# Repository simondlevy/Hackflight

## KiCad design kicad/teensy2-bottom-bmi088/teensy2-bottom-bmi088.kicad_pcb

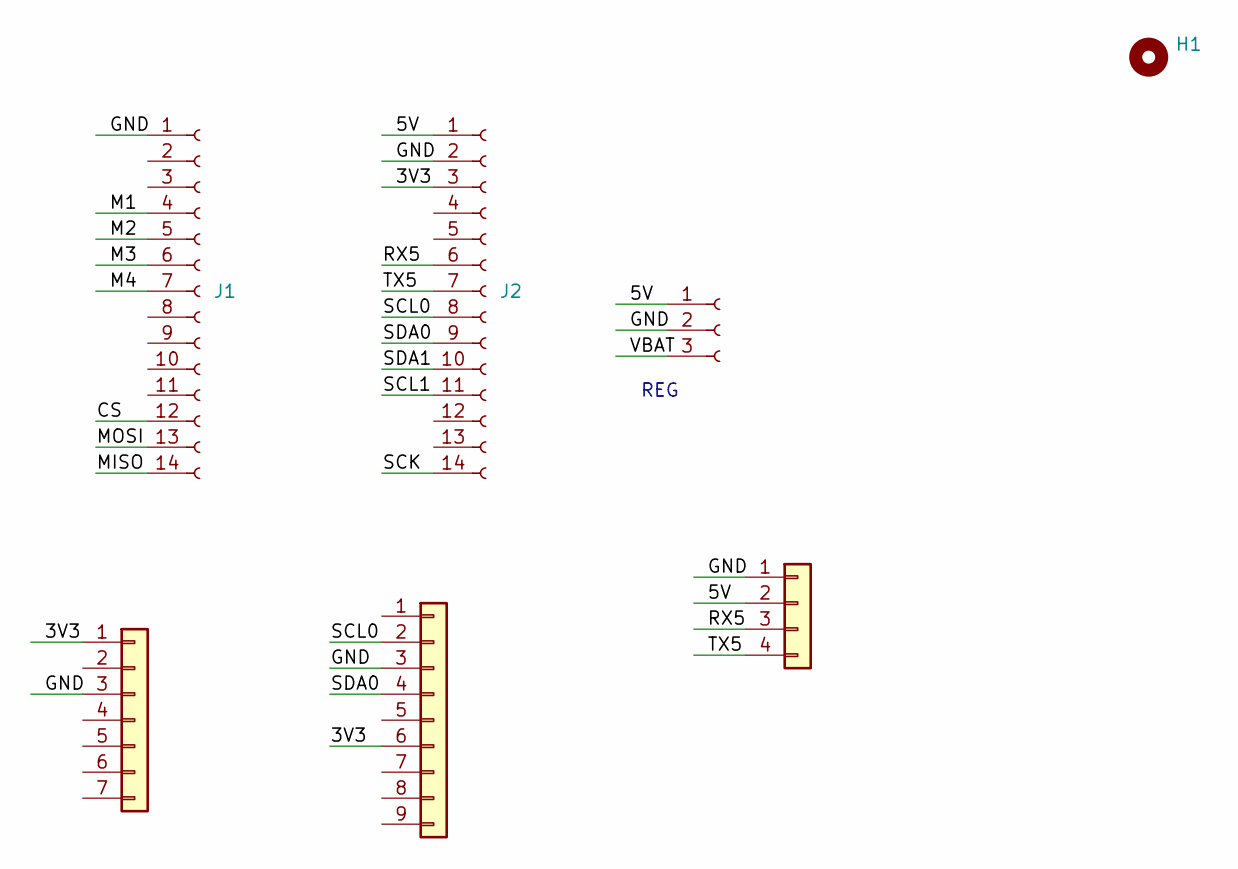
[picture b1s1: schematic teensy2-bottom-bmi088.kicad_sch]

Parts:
H1: MountingHole; MountingHole_2.5mm
J1: Conn_01x14; PinSocket_1x14_P2.54mm_Vertical
J2: Conn_01x14_Socket; PinSocket_1x14_P2.54mm_Vertical
J3: Conn_01x04; PinHeader_1x04_P2.00mm_Vertical
J4: Conn_01x03_Socket; PinHeader_1x03_P2.54mm_Vertical
J7: Conn_01x07; PinHeader_1x07_P1.27mm_Vertical
J8: Conn_01x09; PinHeader_1x09_P1.27mm_Vertical

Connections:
/3V3: J2.3, J7.1, J8.6
/5V: J2.1, J3.2, J4.1
/CS: J1.12
/GND: J1.1, J2.2, J3.1, J4.2, J7.3, J8.3
/M1: J1.4
/M2: J1.5
/M3: J1.6
/M4: J1.7
/MISO: J1.14
/MOSI: J1.13
/RX5: J2.6, J3.3
/SCK: J2.14
/SCL0: J2.8, J8.2
/SCL1: J2.11
/SDA0: J2.9, J8.4
/SDA1: J2.10
/TX5: J2.7, J3.4
/VBAT: J4.3

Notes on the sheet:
REG

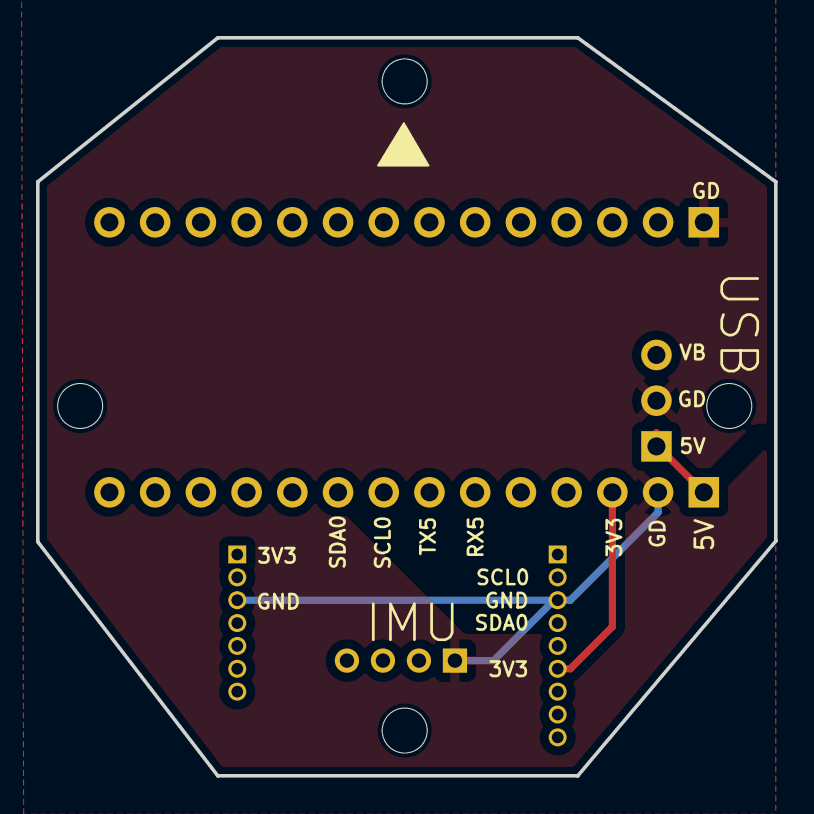
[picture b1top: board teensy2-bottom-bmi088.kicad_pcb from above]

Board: 2 copper layers, 41.0 x 41.0 mm, 8 parts (0 on the bottom side), 7 nets.

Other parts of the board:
H1#2: MountingHole; MountingHole_2.5mm

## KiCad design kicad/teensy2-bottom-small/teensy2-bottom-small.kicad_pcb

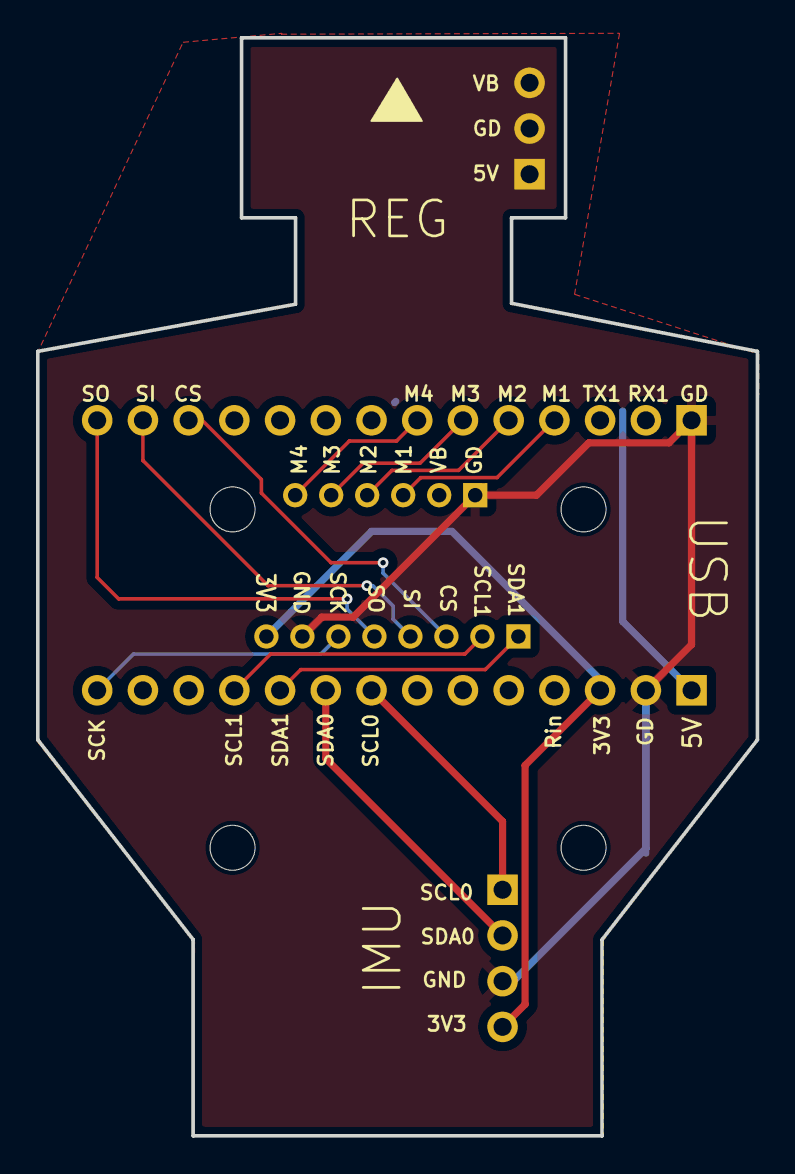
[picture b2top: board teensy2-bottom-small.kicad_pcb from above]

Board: 2 copper layers, 40.0 x 61.0 mm, 10 parts (0 on the bottom side), 16 nets.

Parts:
H1, H2, H3, H4: MountingHole; MountingHole_2.5mm
J1, J2: Conn_01x14_Socket; PinSocket_1x14_P2.54mm_Vertical
J3: Conn_01x04_Socket; PinHeader_1x04_P2.54mm_Vertical
J4: Conn_01x03_Socket; PinHeader_1x03_P2.54mm_Vertical
J5: Conn_01x06_Pin; PinHeader_1x06_P2.00mm_Vertical
J7: Conn_01x08_Pin; PinSocket_1x08_P2.00mm_Vertical

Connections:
/3V3: J2.3, J3.4, J7.8
/5V: J2.1, J4.1
/CS: J1.12, J7.3
/GND: J1.1, J2.2, J3.3, J4.2, J5.1, J7.7
/M1: J1.4, J5.3
/M2: J1.5, J5.4
/M3: J1.6, J5.5
/M4: J1.7, J5.6
/MISO: J1.14, J7.5
/MOSI: J1.13, J7.4
/SCK: J2.14, J7.6
/SCL0: J2.8, J3.1
/SCL1: J2.11, J7.2
/SDA0: J2.9, J3.2
/SDA1: J2.10, J7.1
/VBAT: J4.3, J5.2

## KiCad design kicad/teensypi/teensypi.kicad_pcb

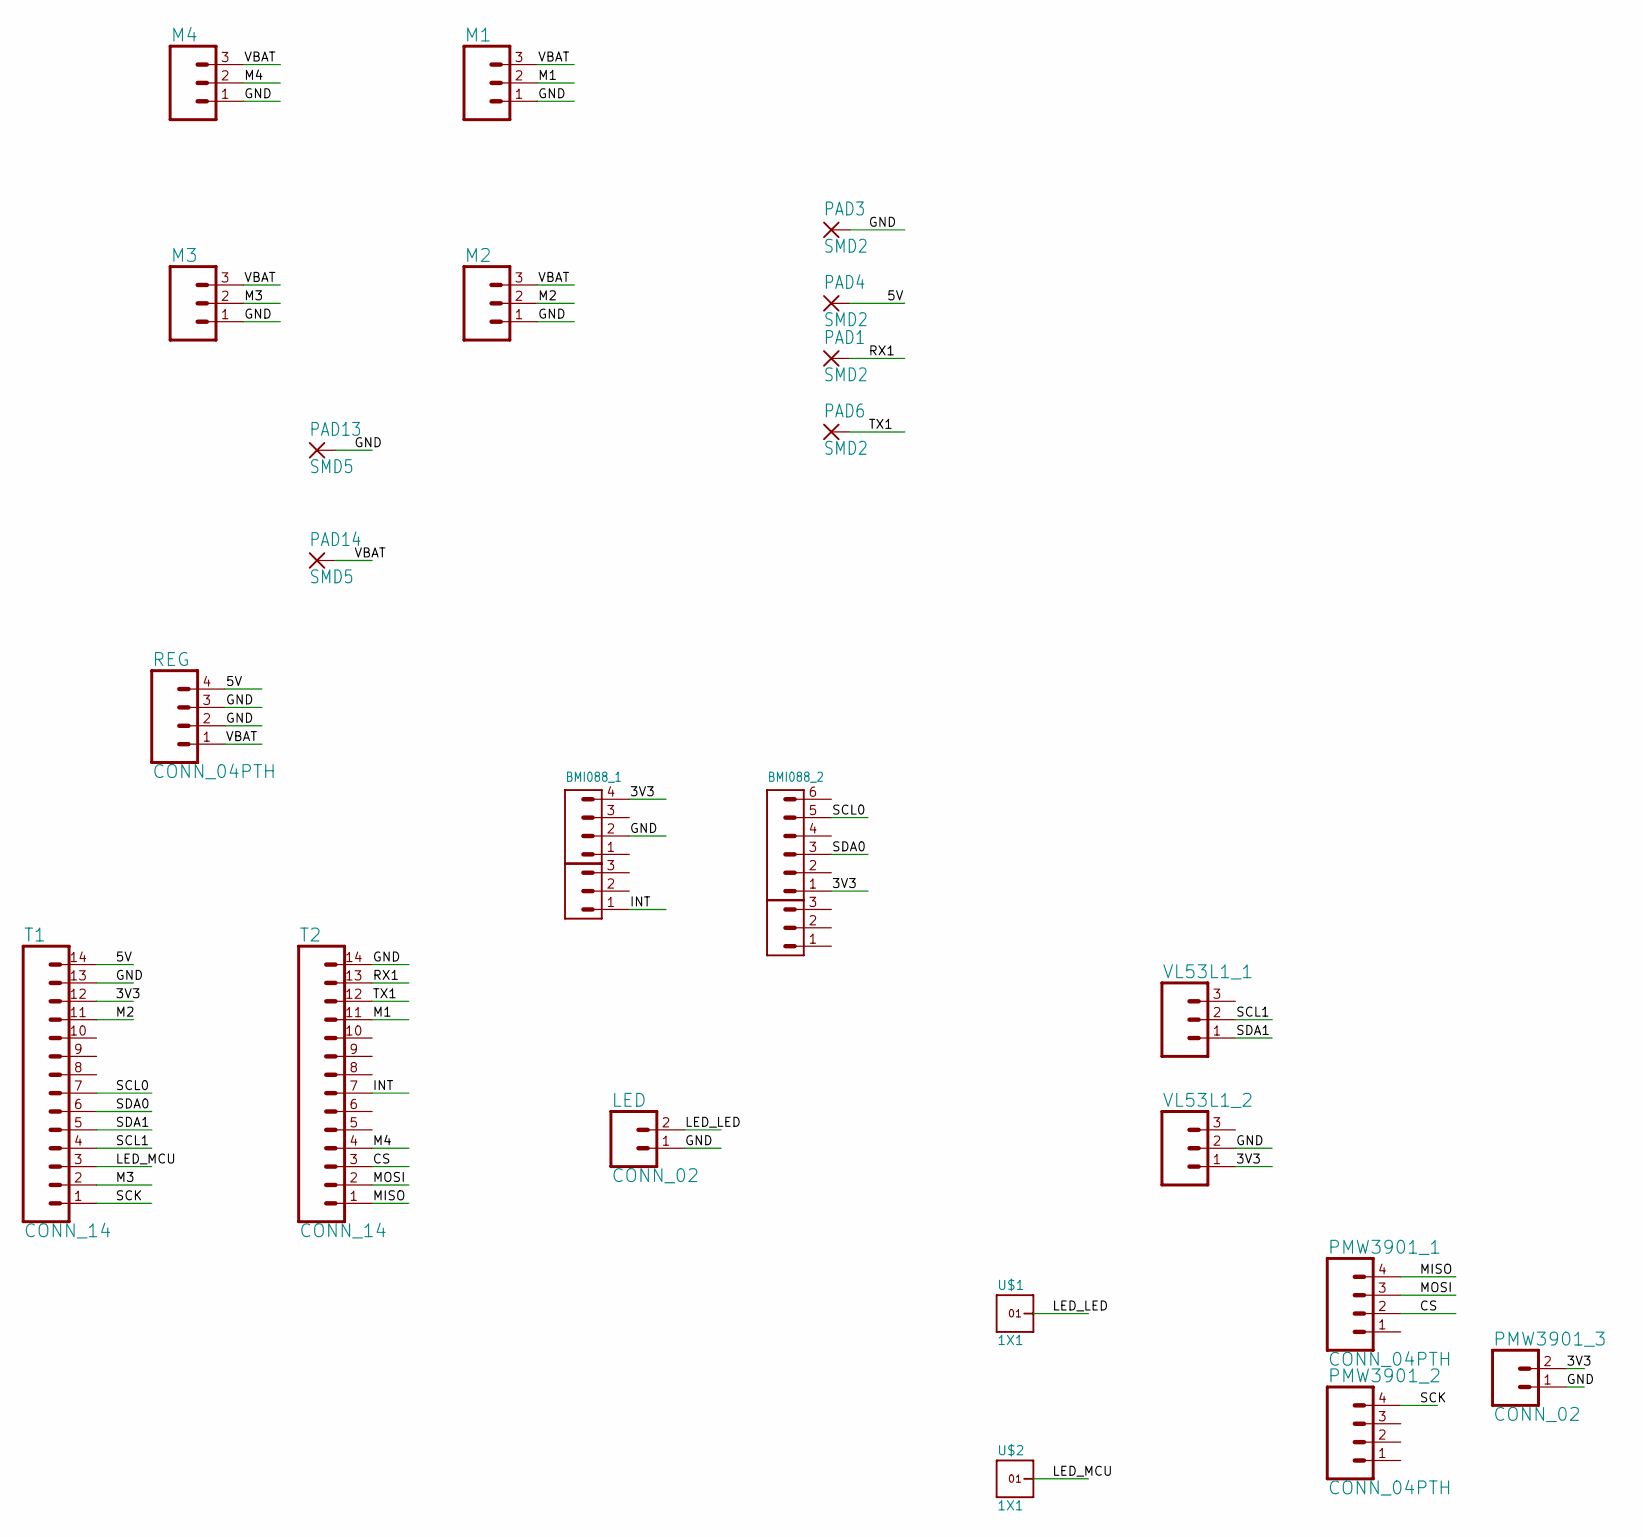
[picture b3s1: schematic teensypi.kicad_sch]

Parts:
BMI088_1: PH1X4-05; PH005-1-4
BMI088_2: PH1X6-05; PH005-1-6
LED: CONN_02; 1X02
M1, M2, M3, M4: 455-1750-1-ND; 1X03
PAD1, PAD3, PAD4, PAD6: SMD2; SMD1,27-2,54
PAD13, PAD14: SMD5; SMD2,54-5,08
PH2, PH3: PH1X3-05; PH005-1-3
PMW3901_1, PMW3901_2: CONN_04PTH; 1X04
PMW3901_3: CONN_02; 1X02
REG: CONN_04PTH; 1X04
T1, T2: CONN_14; 1X14
U$1, U$2: 1X1
VL53L1_1, VL53L1_2: 455-1750-1-ND; 1X03

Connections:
3V3: BMI088_1.4, BMI088_2.1, PMW3901_3.2, T1.12, VL53L1_2.1
5V: PAD4.1, REG.4, T1.14
CS: PMW3901_1.2, T2.3
GND: BMI088_1.2, LED.1, M1.1, M2.1, M3.1, M4.1, PAD3.1, PAD13.1, PMW3901_3.1, REG.2, REG.3, T1.13, T2.14, VL53L1_2.2
INT: PH3.1, T2.7
LED_LED: LED.2, U$1.1
LED_MCU: T1.3, U$2.1
M1: M1.2, T2.11
M2: M2.2, T1.11
M3: M3.2, T1.2
M4: M4.2, T2.4
MISO: PMW3901_1.4, T2.1
MOSI: PMW3901_1.3, T2.2
RX1: PAD1.1, T2.13
SCK: PMW3901_2.4, T1.1
SCL0: BMI088_2.5, T1.7
SCL1: T1.4, VL53L1_1.2
SDA0: BMI088_2.3, T1.6
SDA1: T1.5, VL53L1_1.1
TX1: PAD6.1, T2.12
VBAT: M1.3, M2.3, M3.3, M4.3, PAD14.1, REG.1

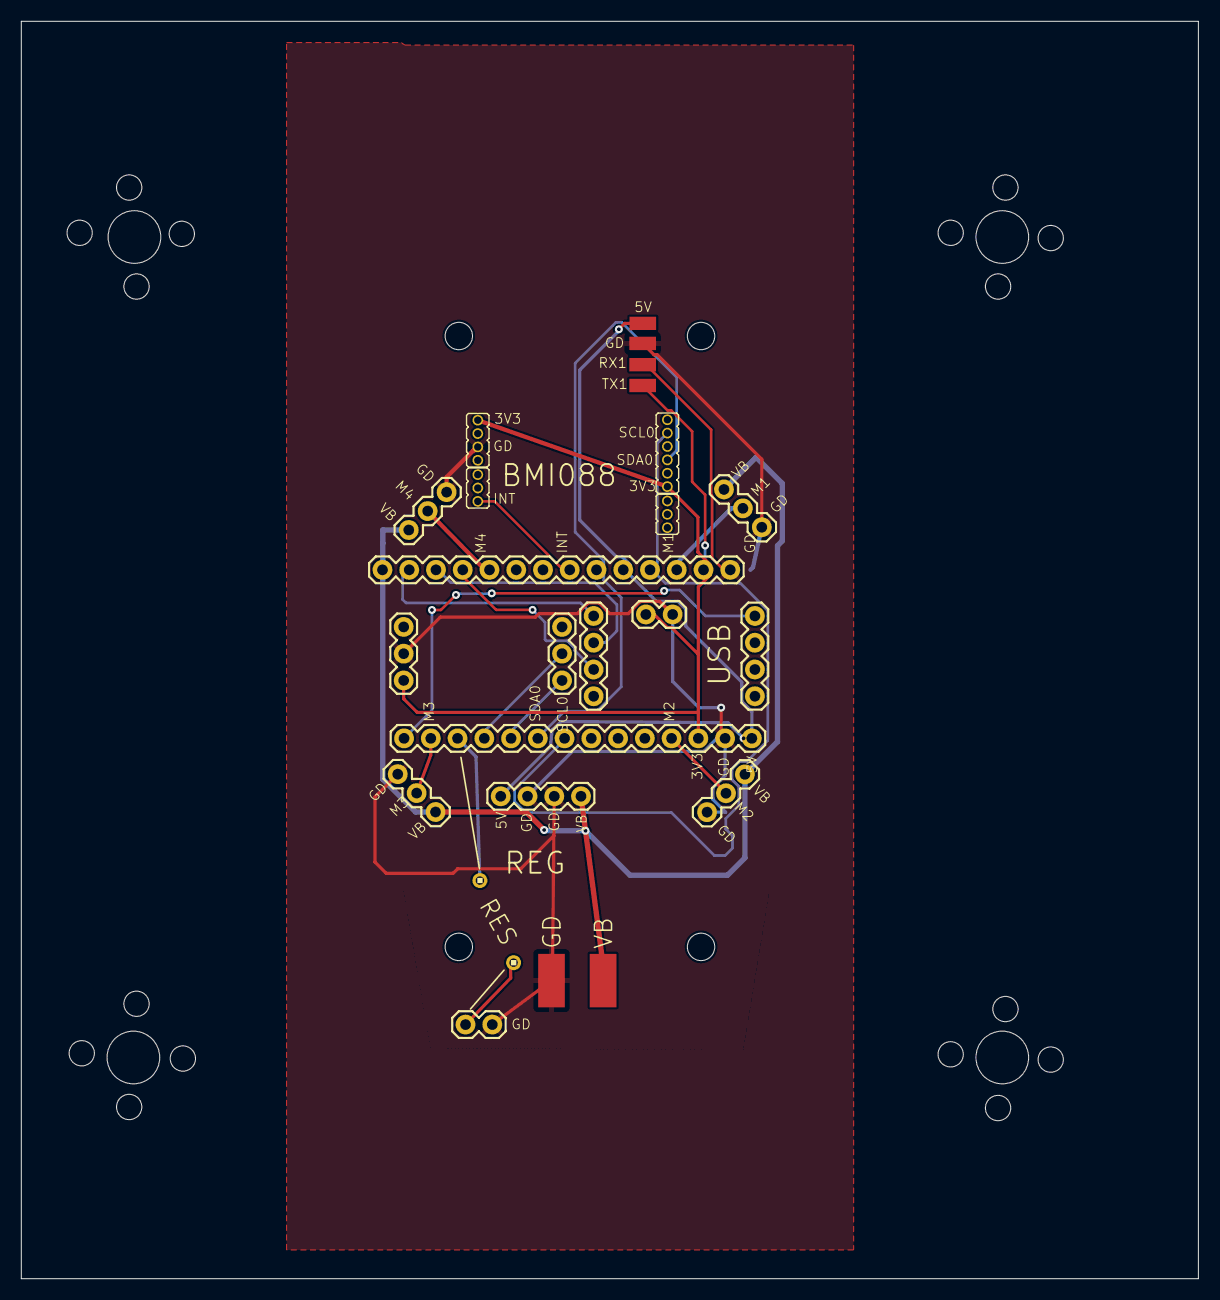
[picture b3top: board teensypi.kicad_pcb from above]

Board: 4 copper layers, 111.8 x 119.4 mm, 49 parts (0 on the bottom side), 21 nets.

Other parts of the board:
@HOLE0, @HOLE1, @HOLE2, @HOLE3, @HOLE4, @HOLE5, @HOLE6, @HOLE7, @HOLE8, @HOLE9, @HOLE10, @HOLE11, @HOLE12, @HOLE13, @HOLE14, @HOLE15, @HOLE16, @HOLE17, @HOLE18, @HOLE19, @HOLE20, @HOLE21, @HOLE22, @HOLE23: (no value)

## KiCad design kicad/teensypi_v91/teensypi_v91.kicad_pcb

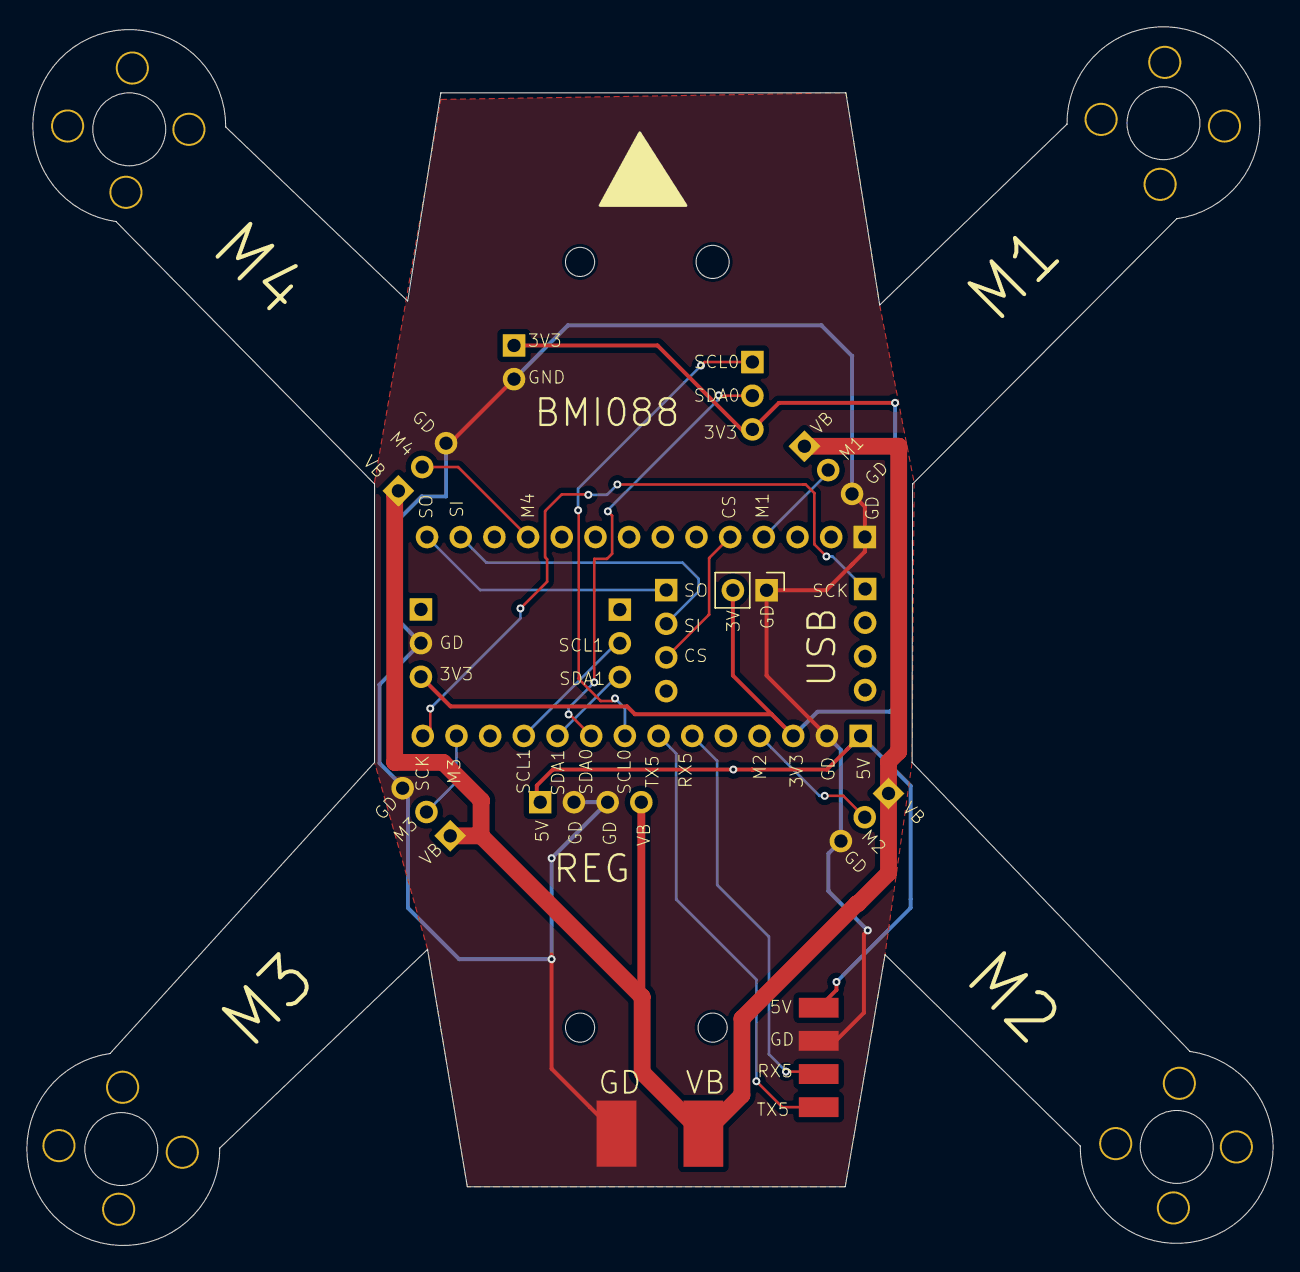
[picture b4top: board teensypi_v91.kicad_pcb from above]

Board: 2 copper layers, 94.0 x 91.9 mm, 44 parts (0 on the bottom side), 18 nets.

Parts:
GND_PAD1, GND_PAD18, GND_PAD19, GND_PAD20, GND_PAD21: Conn_01x01; SolderWirePad_1x01_SMD_5x10mm
M1_center1, M2_center1, M3_center1, M4_center1: MountingHole; MountingHole_5.5mm
M_1_1, M_1_2, M_1_3, M_1_4, M_2_1, M_2_2, M_2_3, M_2_4, M_3_1, M_3_2, M_3_3, M_3_4, M_4_1, M_4_2, M_4_3, M_4_4: MountingHole; MountingHole_2.2mm_M2
Motor5: Conn_01x03_Female; PinHeader_1x03_P2.54mm_Vertical
PMW3901_L1, PMW3901_R1: Conn_01x04_Female; PinSocket_1x04_P2.54mm_Vertical
PMW3901_PWR1, PMW3901_PWR2: Conn_01x02_Female; PinHeader_1x02_P2.54mm_Vertical
POST_1, POST_2, POST_3, POST_4: MountingHole; MountingHole_2.2mm_M2
REG1: Conn_01x04_Female; PinSocket_1x04_P2.54mm_Vertical
Teensy_bottom1: Conn_01x14_Female; PinSocket_1x14_P2.54mm_Vertical
Teensy_top1: Conn_01x14_Female; PinSocket_1x14_P2.54mm_Vertical
VB_PAD1: Conn_01x01; SolderWirePad_1x01_SMD_5x10mm
VL53L1_L1, VL53L1_L2, VL53L1_L3, VL53L1_L4, VL53L1_L5, VL53L1_R1: Conn_01x03_Female; PinHeader_1x03_P2.54mm_Vertical

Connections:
/3V3: Motor5.3, PMW3901_PWR1.2, PMW3901_PWR2.1, Teensy_bottom1.3, VL53L1_L1.3
/5V: GND_PAD19.1, REG1.1, Teensy_bottom1.1
/CS: PMW3901_R1.3, Teensy_top1.5
/GND: GND_PAD1.1, GND_PAD18.1, PMW3901_PWR1.1, PMW3901_PWR2.2, REG1.2, REG1.3, Teensy_bottom1.2, Teensy_top1.1, VL53L1_L1.2, VL53L1_L2.3, VL53L1_L3.3, VL53L1_L4.3, VL53L1_L5.3
/M1: Teensy_top1.4, VL53L1_L2.2
/M2: Teensy_bottom1.4, VL53L1_L3.2
/M3: Teensy_bottom1.13, VL53L1_L5.2
/M4: Teensy_top1.11, VL53L1_L4.2
/MISO: PMW3901_R1.1, Teensy_top1.14
/MOSI: PMW3901_R1.2, Teensy_top1.13
/RX5: GND_PAD20.1, Teensy_bottom1.6
/SCK: PMW3901_L1.1, Teensy_bottom1.14
/SCL0: Motor5.1, Teensy_bottom1.8
/SCL1: Teensy_bottom1.11, VL53L1_R1.2
/SDA0: Motor5.2, Teensy_bottom1.9
/SDA1: Teensy_bottom1.10, VL53L1_R1.3
/TX5: GND_PAD21.1, Teensy_bottom1.7
/VBAT: REG1.4, VB_PAD1.1, VL53L1_L2.1, VL53L1_L3.1, VL53L1_L4.1, VL53L1_L5.1

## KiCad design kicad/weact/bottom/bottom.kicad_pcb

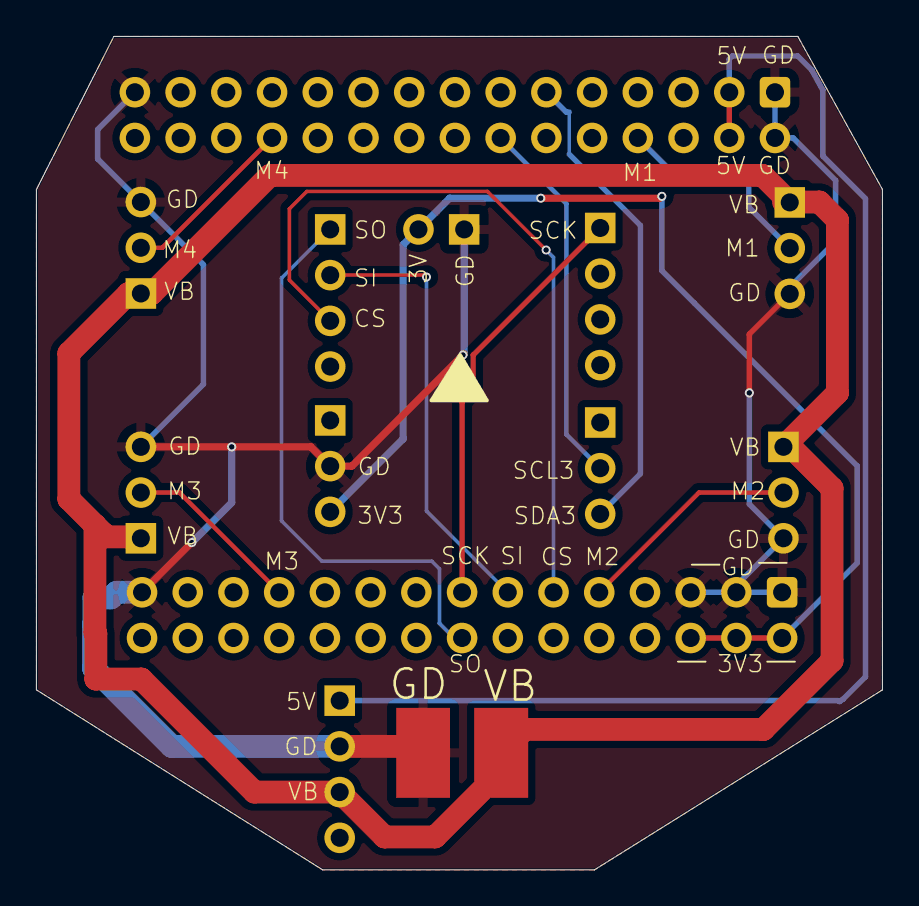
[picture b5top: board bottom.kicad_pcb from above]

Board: 2 copper layers, 47.0 x 46.3 mm, 14 parts (0 on the bottom side), 14 nets.

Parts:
GND_PAD1: Conn_01x01; SolderWirePad_1x01_SMD_5x10mm
J1, J2: Conn_01x15_MountingPin; IDC-Header_2x15_P2.54mm_Vertical
M1_GND1: Conn_01x03_Female; PinHeader_1x03_P2.54mm_Vertical
PMW3901_L1, PMW3901_R1: Conn_01x04_Female; PinSocket_1x04_P2.54mm_Vertical
PMW3901_PWR1: Conn_01x02_Female; PinHeader_1x02_P2.54mm_Vertical
REG1: Conn_01x04_Female; PinSocket_1x04_P2.54mm_Vertical
VB_PAD1: Conn_01x01; SolderWirePad_1x01_SMD_5x10mm
VL53L1_L3, VL53L1_L4, VL53L1_L5, VL53L1_R1, VL53L1_R2: Conn_01x03_Female; PinHeader_1x03_P2.54mm_Vertical

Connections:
/3V3: J2.2, J2.4, J2.6, PMW3901_PWR1.2, VL53L1_R2.3
/5V: J1.3, J1.4, REG1.1
/CS: J2.11, PMW3901_R1.3
/GND: GND_PAD1.1, J1.1, J1.2, J1.29, J2.1, J2.3, J2.5, J2.29, M1_GND1.3, PMW3901_PWR1.1, REG1.2, VL53L1_L3.3, VL53L1_L4.3, VL53L1_L5.3, VL53L1_R2.2
/M1: J1.8, M1_GND1.2
/M2: J2.9, VL53L1_L3.2
/M3: J2.23, VL53L1_L5.2
/M4: J1.24, VL53L1_L4.2
/MISO: J2.16, PMW3901_R1.1
/MOSI: J2.13, PMW3901_R1.2
/SCK: J2.15, PMW3901_L1.1
/SCL3: J1.14, VL53L1_R1.2
/SDA3: J1.11, VL53L1_R1.3
/VBAT: M1_GND1.1, REG1.3, VB_PAD1.1, VL53L1_L3.1, VL53L1_L4.1, VL53L1_L5.1

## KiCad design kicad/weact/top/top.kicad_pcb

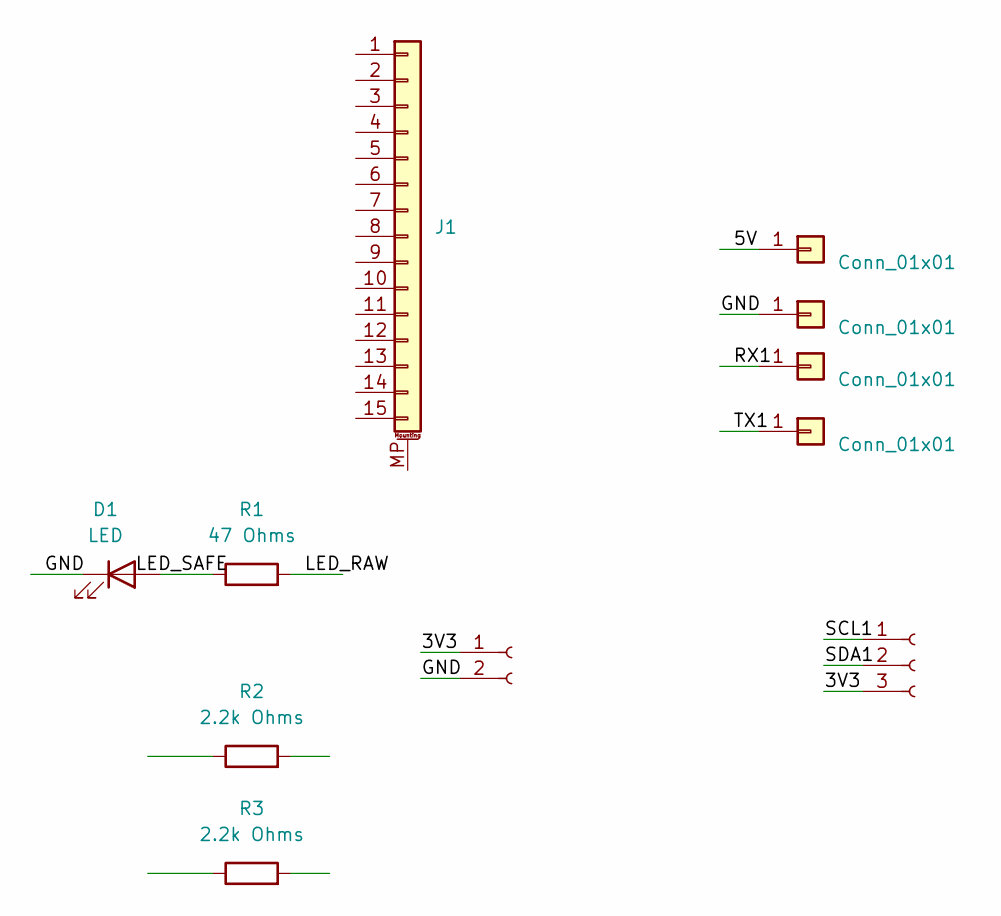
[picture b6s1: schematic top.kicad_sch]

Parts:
D1: LED; LED_D3.0mm
GND_PAD18, GND_PAD19, GND_PAD20, GND_PAD21: Conn_01x01; SolderWirePad_1x01_SMD_5x10mm
J1: Conn_01x15_MountingPin; IDC-Header_2x15_P2.54mm_Vertical
Motor5: Conn_01x03_Female; PinHeader_1x03_P2.54mm_Vertical
PMW3901_PWR2: Conn_01x02_Female; PinHeader_1x02_P2.54mm_Vertical
R1: 47 Ohms; R_Axial_DIN0204_L3.6mm_D1.6mm_P5.08mm_Horizontal
R2, R3: 2.2k Ohms; R_Axial_DIN0204_L3.6mm_D1.6mm_P5.08mm_Horizontal

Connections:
/3V3: J1.2, J1.4, J1.6, Motor5.3, PMW3901_PWR2.1, R2.2, R3.2
/5V: GND_PAD19.1; also elsewhere on the board
/GND: D1.1 (K), GND_PAD18.1, J1.1, J1.3, J1.5, J1.29, PMW3901_PWR2.2; also elsewhere on the board
/LED_RAW: J1.10, R1.2
/RX1: GND_PAD20.1; also elsewhere on the board
/SCL1: Motor5.1, R2.1; also elsewhere on the board
/SDA1: Motor5.2, R3.1; also elsewhere on the board
/TX1: GND_PAD21.1; also elsewhere on the board
unnamed: D1.2 (A), R1.1

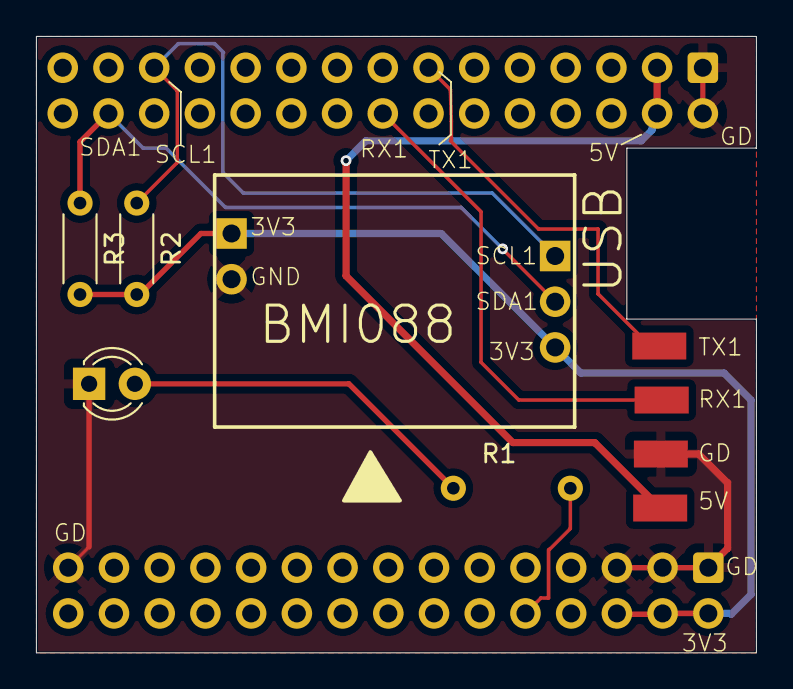
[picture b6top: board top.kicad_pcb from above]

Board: 2 copper layers, 40.0 x 34.2 mm, 12 parts (0 on the bottom side), 9 nets.

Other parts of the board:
J1#2: Conn_01x15_MountingPin; IDC-Header_2x15_P2.54mm_Vertical

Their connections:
/5V: J1#2.3, J1#2.4; also elsewhere on the board
/GND: J1#2.1, J1#2.2; also elsewhere on the board
/RX1: J1#2.16; also elsewhere on the board
/SCL1: J1#2.25; also elsewhere on the board
/SDA1: J1#2.28; also elsewhere on the board
/TX1: J1#2.13; also elsewhere on the board
